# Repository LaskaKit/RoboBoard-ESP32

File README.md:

# LaskaKit RoboBoard ESP32
Build a robot! Don't worry, it's nothing complicated. It's easy with our RoboBoard-ESP32. The RoboBoard has everything you need for a simple robot on it, and you can make it into a much more complex robot over time thanks to the expansion connectors for both the I2C and SPI bus. 

You can connect a lot of other peripherals. 

The basis of the whole board is ESP32 - it hides a great performance, the possibility to use Wi-Fi or Bluetooth interface and also a large community of DIY makers who have already invented many projects with it. It is not something unknown - ESP32 is one of the most well-known and used modules ever. 

The RoboBoard-ESP32 has a ready-to-use programmer (CH9102F), just plug the USB-C cable into the board and your computer, start the Arduino IDE and you can start programming. The converter-programmer will take care of uploading the program to the ESP32. 

The RoboBoard-ESP32 can drive up to 4 DC motors using PWM, thanks to the TB6612 driver. The maximum continuous current through one channel is 1A. The TB6612 DC motor driver is controlled via the PCA9685, which is controlled via the I2C bus. So you only need two wires (I2C, SDA - GPIO21 and SCL - GPIO22) to drive up to 4 DC motors. 

If you don't want to use DC motors or on the contrary you would like to add Servos to them, RoboBoard-ESP32 is ready for this option as well. 
You can connect up to 8 servo motors - what you use the servo motors for is up to you. The individual servo motors are controlled by GPIO16 to GPIO19, then GPIO25 and GPIO26 and lastly GPIO32 and GPIO33. 

What else have we prepared on the board? We have fitted a buzzer, you can control it via GPIO27. Then we have fitted two I2C ushup connectors to connect I2C sensors that are powered by 3.3V (SDA - GPIO21 and SCL - GPIO22) and one SPI ushup to connect other sensors or displays powered by 3.3V (CS - GPIO15, SDI/MOSI - GPIO13, CLK - GPIO14, SDO/MISO - GPIO12).

For the battery, we have a standard 3-pin JST-XH-3P connector where you plug in 2S LiPol batteries - for example this one https://www.laskakit.cz/rc-lipol-baterie-2s-1000mah-7-4v-20c-jst-bec/

The motors are powered via the LMR14050 step-down switching inverter from the 2S battery, which can deliver up to 5A. 

The battery voltage, via the voltage divider, is fed and measured by GPIO34. 

## New in version 2
- Powering via USB
- LiPol charging via USB
- uŠup IO port
- SK6812 RGB LED
- Overall more robust design

Sample codes will be prepared on our github at https://github.com/LaskaKit/RoboBoard-ESP32/tree/main/SW

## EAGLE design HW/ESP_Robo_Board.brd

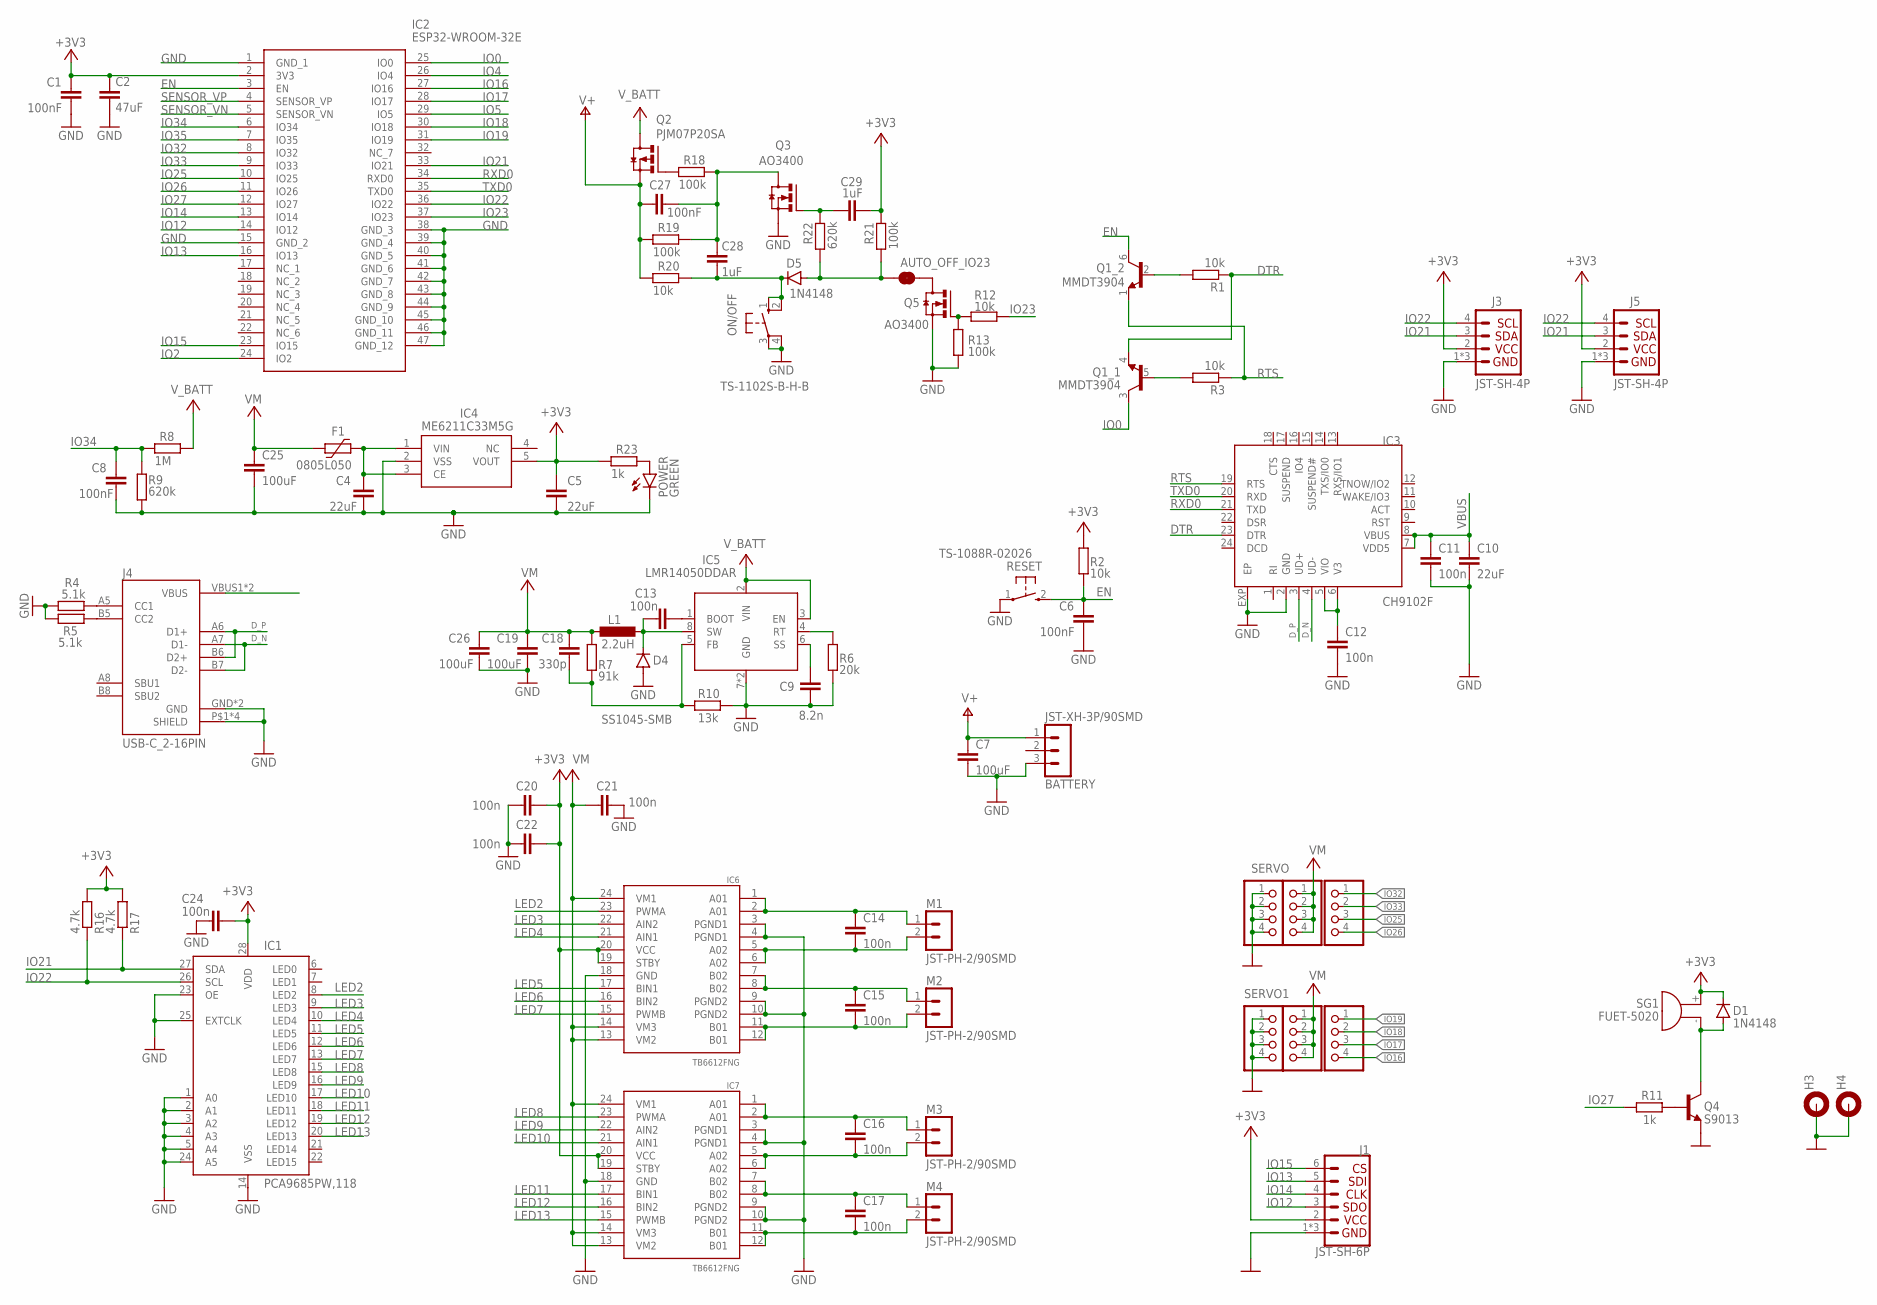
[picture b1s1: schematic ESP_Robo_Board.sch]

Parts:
1, 5: PINHD_1X4_RED; 1X04
2, 6: PINHD_1X4_BLACK; 1X04
AUTO_OFF_IO23: nv; SMT-JUMPER_2_NC_TRACE_SILK
BATTERY: JST-XH-3P/90SMD; S3B-XH-SM4
C1: 100nF; C0603
C2: 47uF; C0805
C4, C10: 22uF; C0603
C5: 22uF; C0603; LCSC_PART C19666
C6, C8, C27: 100nF; C0402
C7, C19, C25, C26: 100uF; C1206
C9: 8.2n; C0603
C11, C12: 100n; C0402
C13, C14, C15, C16, C17, C20, C21, C22, C24: 100n; C0603
C18: 330p; C0402
C28, C29: 1uF; C0603
D1: 1N4148; SOD323-R; LCSC_PART C94001
D4: SS1045-SMB; SMB; LCSC_PART C2903947
D5: 1N4148; SOD323-R
F1: 0805L050; 0805L; LCSC_PART C66452
H3, H4: MOUNT-PAD-ROUND2.5; 2,5-PAD
IC1: PCA9685PW,118; TSSOP28
IC2: ESP32-WROOM-32E; ESP32WROOM32E
IC3: CH9102F; QFN24-4X4
IC4: ME6211C33M5G; SOT23-5
IC5: LMR14050DDAR; SO08-EPAD
IC6, IC7: TB6612FNG; SSOP24
J1: JST-SH-6P; 1X06_1MM_RA_VERT
J3, J5: JST-SH-4P; 1X04_1MM_RA_VERT
J4: USB-C_2-16PIN; USBC_USB-C-16P-5
L1: 2.2uH; L5.4X5.2; LCSC_PART C351096
M1, M2, M3, M4: JST-PH-2/90SMD; S2B-PH-SM4
ON/OFF: TS-1102S-B-H-B; B3F-SMD
POWER: GREEN; CHIPLED_0402
Q1: MMDT3904; SC70-6; LCSC_PART C268586
Q2: PJM07P20SA; SOT23; LCSC_PART C2856842
Q3, Q5: AO3400; SOT23; LCSC_PART C693097
Q4: S9013; SOT23-BEC; LCSC_PART C52801
R1, R2, R3, R12, R20: 10k; R0402
R4, R5: 5.1k; R0402
R6: 20k; R0402
R7: 91k; R0402
R8: 1M; R0402
R9, R22: 620k; R0402
R10: 13k; R0402
R11: 1k; R0402; LCSC_PART C22548
R13, R18, R19, R21: 100k; R0402
R16, R17: 4.7k; R0402
R23: 1k; R0402
RESET: TS-1088R-02026; TS1088R02026; LCSC_PART C455280
SERVO, SERVO1: PINHD_1X4_YELLOW; 1X04
SG1: FUET-5020

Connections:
+3V3: C1.1, C2.1, C5.1, C20.2, C22.2, C24.2, C29.1, D1.C, IC1.28 (VDD), IC2.2 (3V3), IC4.5 (VOUT), IC6.19 (STBY), IC6.20 (VCC), IC7.19 (STBY), IC7.20 (VCC), J1.2 (VCC), J3.2 (VCC), J5.2 (VCC), R2.1, R16.2, R17.2, R21.2, R23.1, SG1.+
+6V: 1.1, 1.2, 1.3, 1.4, 5.1, 5.2, 5.3, 5.4, C18.1, C19.1, C21.1, C25.1, C26.1, F1.2, IC6.13 (VM2), IC6.14 (VM3), IC6.24 (VM1), IC7.13 (VM2), IC7.14 (VM3), IC7.24 (VM1), L1.2, R7.1
DTR: IC3.23 (DTR), Q1.4 (E), R1.1
D_N: IC3.4 (UD-), J4.A7 (D1-), J4.B7 (D2-)
D_P: IC3.3 (UD+), J4.A6 (D1+), J4.B6 (D2+)
EN: C6.1, IC2.3 (EN), Q1.6 (C), R2.2, RESET.2 (3)
GND: 2.1, 2.2, 2.3, 2.4, 6.1, 6.2, 6.3, 6.4, BATTERY.3 (1), C1.2, C2.2, C4.2, C5.2, C6.2, C7.2, C8.2, C9.2, C10.2, C11.2, C12.2, C19.2, C20.1, C21.2, C22.1, C24.1, C25.2, C26.2, D4.A, H3.1, H4.1, IC1.1 (A0), IC1.2 (A1), IC1.3 (A2), IC1.4 (A3), IC1.5 (A4), IC1.14 (VSS), IC1.23 (OE), IC1.24 (A5), IC1.25 (EXTCLK), IC2.1 (GND_1), IC2.15 (GND_2), IC2.38 (GND_3), IC2.39 (GND_4), IC2.40 (GND_5), IC2.41 (GND_6), IC2.42 (GND_7), IC2.43 (GND_8), IC2.44 (GND_9), IC2.45 (GND_10), IC2.46 (GND_11), IC2.47 (GND_12), IC3.2 (GND), IC3.EXP (EP), IC4.2 (VSS), IC5.7 (GND), IC5.EPAD (GND), IC6.3 (PGND1), IC6.4 (PGND1), IC6.9 (PGND2), IC6.10 (PGND2), IC6.18 (GND), IC7.3 (PGND1), IC7.4 (PGND1), IC7.9 (PGND2), IC7.10 (PGND2), IC7.18 (GND), J1.1 (GND), J1.NC1 (GND), J1.NC2 (GND), J3.1 (GND), J3.NC1 (GND), J3.NC2 (GND), J4.GND, J4.GND2 (GND), J4.P$1 (SHIELD), J4.P$2 (SHIELD), J4.P$3 (SHIELD), J4.P$4 (SHIELD), J5.1 (GND), J5.NC1 (GND), J5.NC2 (GND), ON/OFF.3, ON/OFF.4 (P1), POWER.C, Q3.2 (S), Q4.E, Q5.2 (S), R4.1, R5.1, R6.2, R9.1, R10.2, R13.1, RESET.1
IO0: IC2.25 (IO0), Q1.3 (C)
IO2: IC2.24 (IO2)
IO4: IC2.26 (IO4)
IO5: IC2.29 (IO5)
IO12: IC2.14 (IO12), J1.3 (SDO)
IO13: IC2.16 (IO13), J1.5 (SDI)
IO14: IC2.13 (IO14), J1.4 (CLK)
IO15: IC2.23 (IO15), J1.6 (CS)
IO16: IC2.27 (IO16), SERVO1.4
IO17: IC2.28 (IO17), SERVO1.3
IO18: IC2.30 (IO18), SERVO1.2
IO19: IC2.31 (IO19), SERVO1.1
IO21: IC1.27 (SDA), IC2.33 (IO21), J3.3 (SDA), J5.3 (SDA), R17.1
IO22: IC1.26 (SCL), IC2.36 (IO22), J3.4 (SCL), J5.4 (SCL), R16.1
IO23: IC2.37 (IO23), R12.2
IO25: IC2.10 (IO25), SERVO.3
IO26: IC2.11 (IO26), SERVO.4
IO27: IC2.12 (IO27), R11.1
IO32: IC2.8 (IO32), SERVO.1
IO33: IC2.9 (IO33), SERVO.2
IO34: C8.1, IC2.6 (IO34), R8.1, R9.2
IO35: IC2.7 (IO35)
LED2: IC1.8 (LED2), IC6.23 (PWMA)
LED3: IC1.9 (LED3), IC6.22 (AIN2)
LED4: IC1.10 (LED4), IC6.21 (AIN1)
LED5: IC1.11 (LED5), IC6.17 (BIN1)
LED6: IC1.12 (LED6), IC6.16 (BIN2)
LED7: IC1.13 (LED7), IC6.15 (PWMB)
LED8: IC1.15 (LED8), IC7.23 (PWMA)
LED9: IC1.16 (LED9), IC7.22 (AIN2)
LED10: IC1.17 (LED10), IC7.21 (AIN1)
LED11: IC1.18 (LED11), IC7.17 (BIN1)
LED12: IC1.19 (LED12), IC7.16 (BIN2)
LED13: IC1.20 (LED13), IC7.15 (PWMB)
unnamed: C4.1, F1.1, IC4.1 (VIN), IC4.3 (CE)
unnamed: J4.A5 (CC1), R4.2
unnamed: C13.1, D4.C, IC5.8 (SW), L1.1
unnamed: Q1.5 (B), R3.2
unnamed: C9.1, IC5.6 (SS)
unnamed: IC5.4 (RT), R6.1
unnamed: J4.B5 (CC2), R5.2
unnamed: Q4.B, R11.2
unnamed: POWER.A, R23.2
unnamed: C13.2, IC5.1 (BOOT)
unnamed: Q1.2 (B), R1.2
unnamed: Q5.1 (G), R12.1, R13.2
unnamed: D1.A, Q4.C, SG1.-
unnamed: C12.1, IC3.5 (VIO), IC3.6 (V3)
unnamed: AUTO_OFF_IO23.2, Q5.3 (D)
unnamed: C18.2, IC5.5 (FB), R7.2, R10.1
unnamed: C14.1, IC6.1 (A01), IC6.2 (A01), M1.1
unnamed: C14.2, IC6.5 (A02), IC6.6 (A02), M1.2
unnamed: C15.1, IC6.7 (B02), IC6.8 (B02), M2.1
unnamed: Q2.1 (G), R18.1
unnamed: C15.2, IC6.11 (B01), IC6.12 (B01), M2.2
unnamed: C16.1, IC7.1 (A01), IC7.2 (A01), M3.1
unnamed: C28.2, D5.C, ON/OFF.1 (S), ON/OFF.2 (S1), R20.2
unnamed: C16.2, IC7.5 (A02), IC7.6 (A02), M3.2
unnamed: C17.1, IC7.7 (B02), IC7.8 (B02), M4.1
unnamed: C27.2, C28.1, Q3.3 (D), R18.2, R19.2
unnamed: C17.2, IC7.11 (B01), IC7.12 (B01), M4.2
unnamed: C29.2, Q3.1 (G), R22.2
unnamed: AUTO_OFF_IO23.1, D5.A, R21.1, R22.1
RTS: IC3.19 (RTS), Q1.1 (E), R3.1
RXD0: IC2.34 (RXD0), IC3.21 (TXD)
SENSOR_VN: IC2.5 (SENSOR_VN)
SENSOR_VP: IC2.4 (SENSOR_VP)
TXD0: IC2.35 (TXD0), IC3.20 (RXD)
V+: BATTERY.1 (3), C7.1, C27.1, Q2.2 (S), R19.1, R20.1
VBUS: C10.1, C11.1, IC3.7 (VDD5), IC3.8 (VBUS), J4.VBUS1 (VBUS), J4.VBUS2 (VBUS)
V_BATT: IC5.2 (VIN), IC5.3 (EN), Q2.3 (D), R8.2

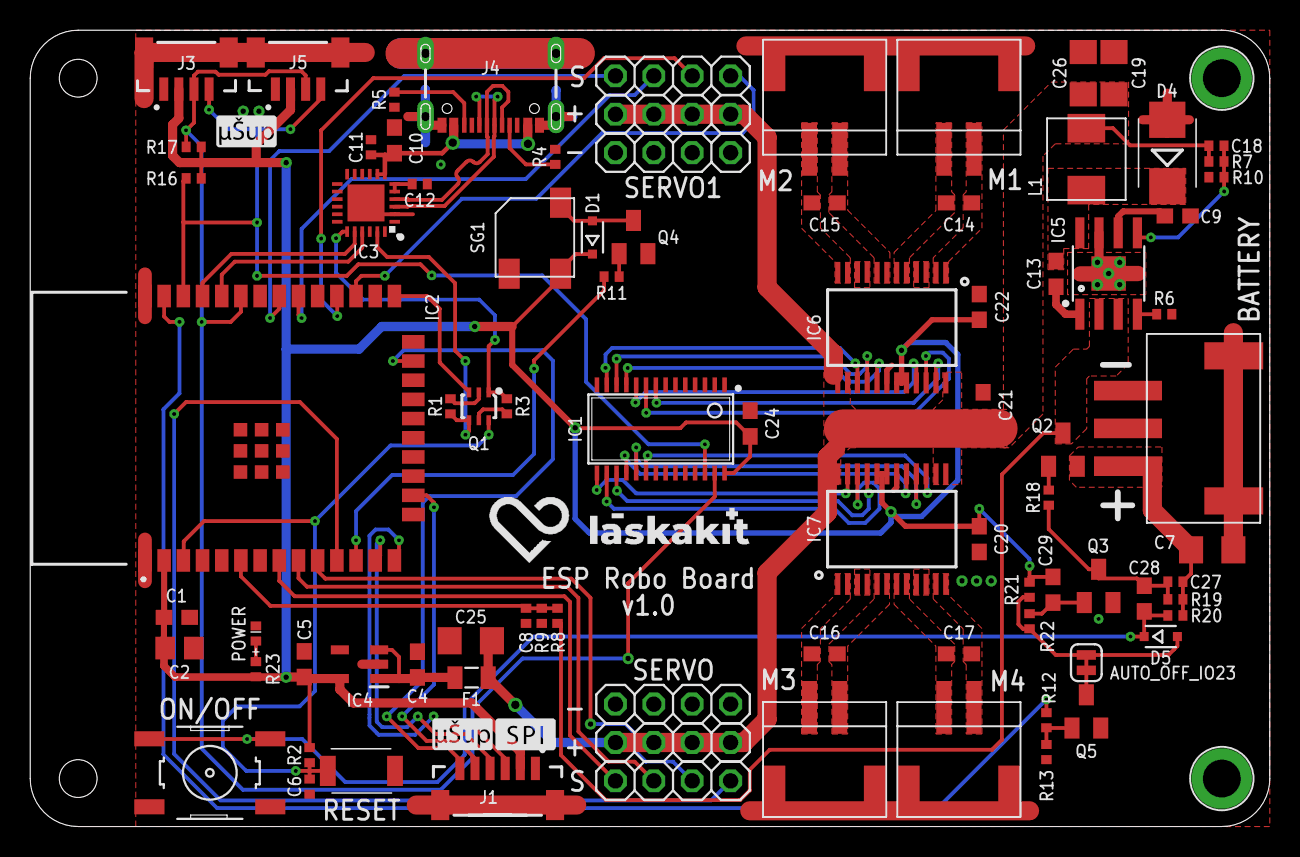
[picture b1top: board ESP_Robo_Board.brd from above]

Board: 2 copper layers, 82.0 x 52.7 mm, 91 parts (0 on the bottom side), 72 nets.

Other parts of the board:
U$1, U$2: USUP_4MM_SILKSCREEN
U$3: LASKKIT_20MM_SILKSCREEN
U$4: SPI_4MM_SILKSCREEN

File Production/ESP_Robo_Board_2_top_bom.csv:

Comment,Designator,Footprint,LCSC Part #
1M,R8,R0402,
1N4148,D1 D5,SOD323-R,
1k,R11 R23,R0402,
1uF,C28 C29,C0603,
2.2uH,L1,L5.4X5.2,C351096
4.7k,R16 R17,R0402,
5.1k,R4 R5,R0402,
8.2n,C9,C0603,
10k,R1 R2 R3 R12 R20,R0402,
13k,R10,R0402,
20k,R6,R0402,
22uF,C4 C5 C10,C0603,
47uF,C2,C0805,
91k,R7,R0402,
100k,R13 R18 R19 R21,R0402,
100n,C11 C12,C0402,
100n,C13 C14 C15 C16 C17 C20 C21 C22 C24,C0603,
100nF,C1,C0603,
100nF,C6 C8 C27,C0402,
100uF,C7 C19 C25 C26,C1206,
330p,C18,C0402,
620k,R9 R22,R0402,
0805L050,F1,0805L,C66452
AO3400,Q3 Q5,SOT23,C693097
CH9102F,IC3,QFN24-4X4,
ESP32-WROOM-32E,IC2,ESP32WROOM32E,
FUET-5020,SG1,FUET-5020,C391029
GREEN,POWER,CHIPLED_0402,
JST-PH-2/90SMD,M1 M2 M3 M4,S2B-PH-SM4,C47647
JST-SH-4P,J3 J5,1X04_1MM_RA_VERT,C371588
JST-SH-6P,J1,1X06_1MM_RA_VERT,C145963
JST-XH-3P/90SMD,BATTERY,S3B-XH-SM4,
LMR14050DDAR,IC5,SO08-EPAD,C155484
ME6211C33M5G,IC4,SOT23-5,
MMDT3904,Q1,SC70-6,C268586
PCA9685PW 118,IC1,TSSOP28,C2678753
PJM07P20SA,Q2,SOT23,C2856842
S9013,Q4,SOT23-BEC,C52801
SS1045-SMB,D4,SMB,C2903947
TB6612FNG,IC6 IC7,SSOP24,
TS-1088R-02026,RESET,TS1088R02026,C455280
TS-1102S-B-H-B,ON/OFF,B3F-SMD,
USB-C_2-16PIN,J4,USBC_USB-C-16P-5,C2837092

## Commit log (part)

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2023-11-30 correct photos
2023-12-26 Update README_CZ.md
    added pinout
2023-12-26 Update README.md
    added pinout
2025-04-25 Add SW example using omni wheels and gamepad.
2025-05-02 Revisit gamepad code. Add a small header lib.
2025-05-09 Add beacon. Update car and gamepad.
2025-05-10 Disable the auto off feature when vbat is low.
2025-05-16 Implement secure communication. Refactor.
2025-05-23 Keep one ESP-NOW peer. Add timed power off button.
2025-05-23 Update.
2025-05-23 Add image
2025-05-23 Add a header
2025-05-23 Describe the controls.
2025-10-19 new ver
2026-01-09 moved
2026-01-09 renamed
2026-01-09 delete
2026-01-09 new ver v2
2026-01-12 description update

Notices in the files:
parts and their libraries:
LaskaKit-Jumpers: Licensing: Creative Commons ShareAlike 4.0 International - https://creativecommons.org/licenses/by-sa/4.0
